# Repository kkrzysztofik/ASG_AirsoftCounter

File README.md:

Schemat mocno uproszczony, bez masy, ani zasilania. Same kable sygnałowe. Do otworzenia w progamie http://fritzing.org/home/

Budowa i części opisane w temacie:
https://forbot.pl/forum/topic/12780-airsoftowy-gadzet-koparka-airsoftcoin/

Filmik z działania: https://www.youtube.com/watch?v=qoA_SEkDOQQ

Przy pierwszym uruchomieniu trzeba odkomentować linijkę 27 z pliku System.cpp, żeby wgrać podstawowe ustawienia. Następnie trzeba uruchomić urządzenie, zakomentować linijkę ponownie i wgrać program ponownie. Dopiero wtedy zapis ustawień będzie działał poprawnie. 

Licencja mit, więc można budować, przerabiać, a nawet sprzedawać.

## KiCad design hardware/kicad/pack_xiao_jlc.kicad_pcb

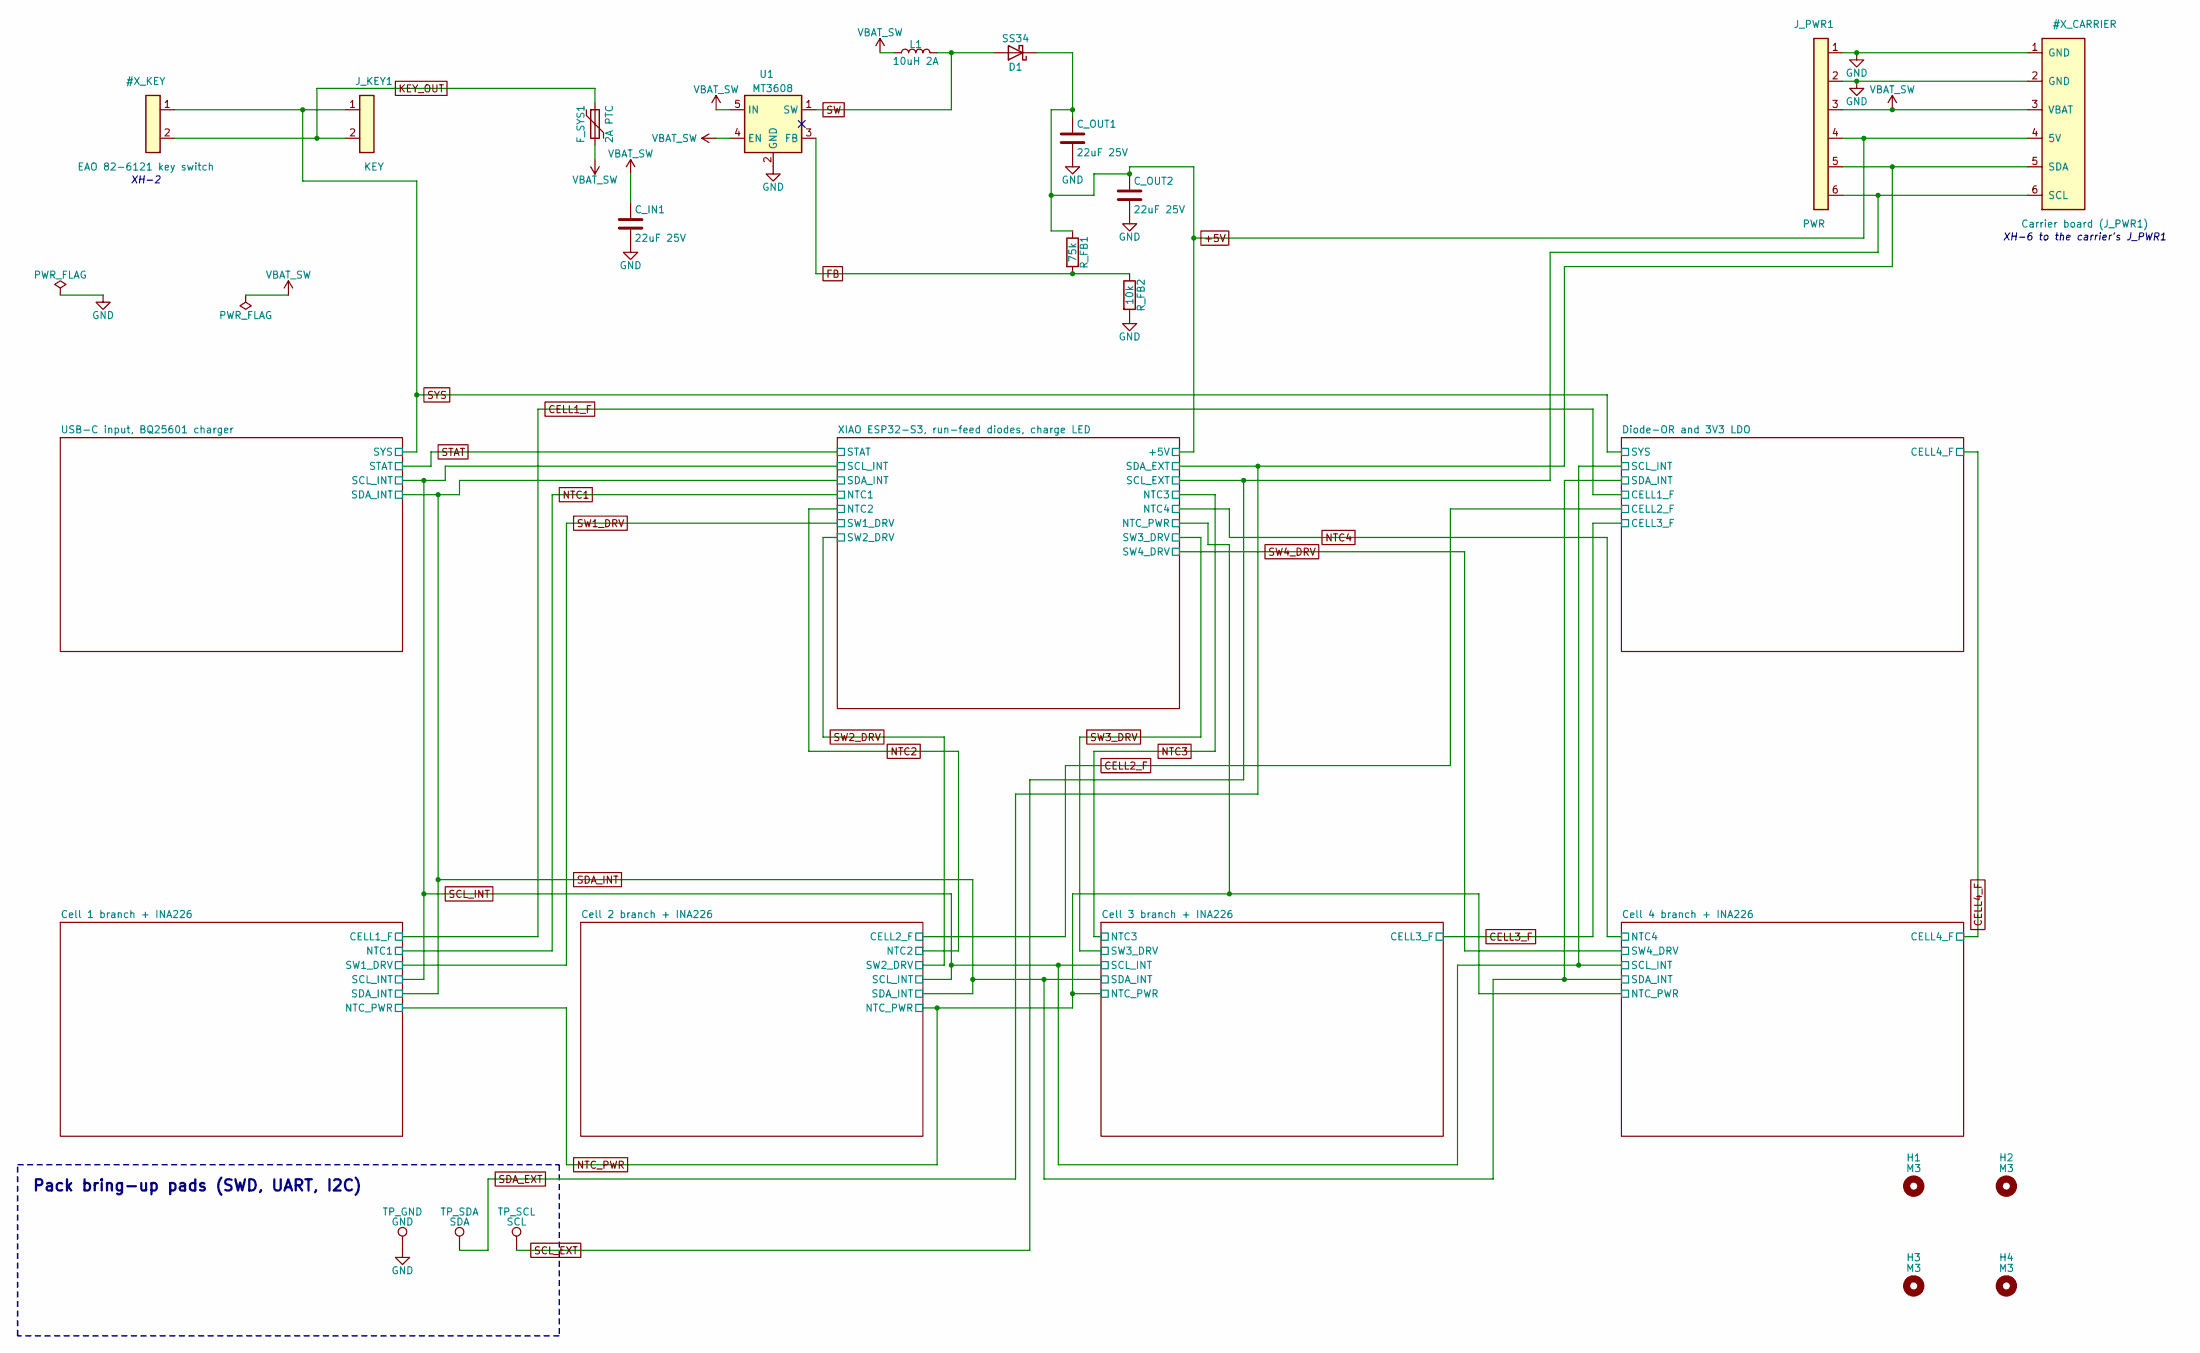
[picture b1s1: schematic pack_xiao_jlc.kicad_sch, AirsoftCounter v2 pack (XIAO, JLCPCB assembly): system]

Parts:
C_IN1: 22uF 25V; C_1206_3216Metric_Pad1.33x1.80mm_HandSolder
C_OUT1, C_OUT2: 22uF 25V; C_1206_3216Metric_Pad1.33x1.80mm_HandSolder
D1: SS34; D_SMA
F_SYS1: 2A PTC; Fuse_1206_3216Metric_Pad1.42x1.75mm_HandSolder
H1, H2, H3, H4: M3; MountingHole_3.2mm_M3
J_KEY1: KEY; JST_XH_B2B-XH-A_1x02_P2.50mm_Vertical
J_PWR1: PWR; JST_XH_B6B-XH-A_1x06_P2.50mm_Vertical
L1: 10uH 2A; L_Bourns_SRN6045TA
R_FB1: 75k; R_0805_2012Metric_Pad1.20x1.40mm_HandSolder
R_FB2: 10k; R_0805_2012Metric_Pad1.20x1.40mm_HandSolder
TP_GND: GND; TestPoint_Pad_D1.5mm
TP_SCL: SCL; TestPoint_Pad_D1.5mm
TP_SDA: SDA; TestPoint_Pad_D1.5mm
U1: MT3608; SOT-23-6

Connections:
FB: R_FB1.2, R_FB2.1, U1.3 (FB)
SW: D1.2 (A), L1.2, U1.1 (SW)

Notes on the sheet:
XH-6 to the carrier's J_PWR1
XH-2
Pack bring-up pads (SWD, UART, I2C)

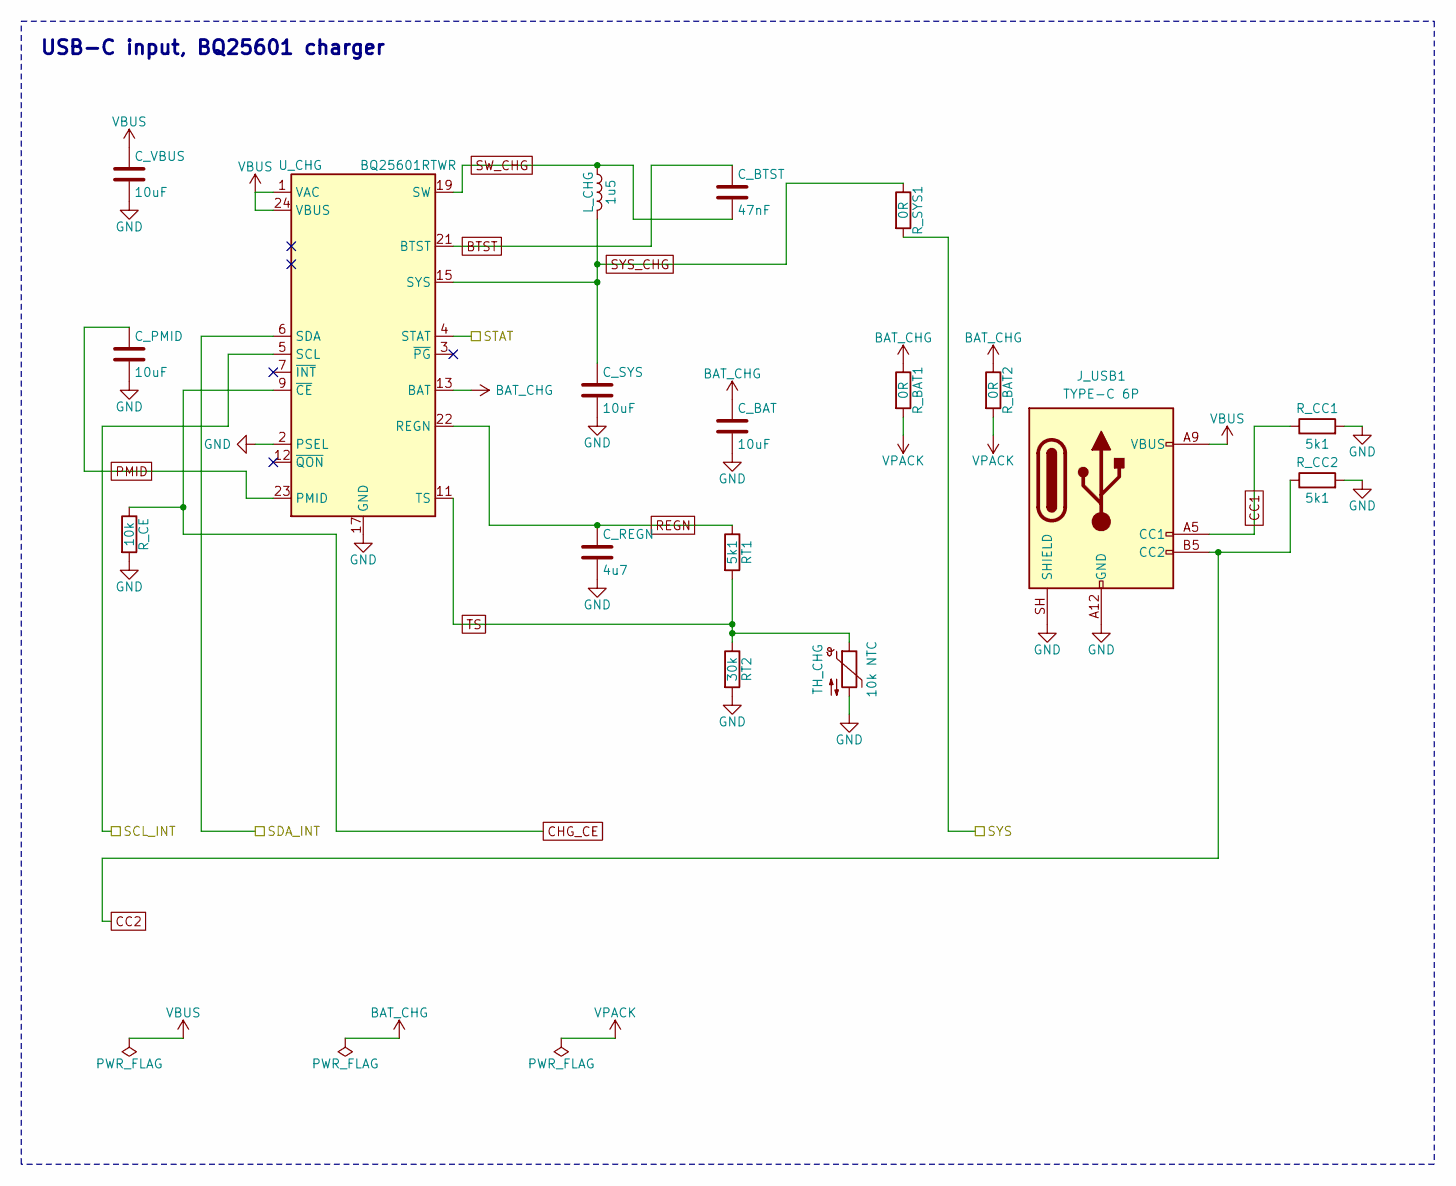
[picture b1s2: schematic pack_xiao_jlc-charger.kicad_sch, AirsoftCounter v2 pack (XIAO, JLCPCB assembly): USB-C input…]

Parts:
C_BAT: 10uF; C_0805_2012Metric_Pad1.18x1.45mm_HandSolder
C_BTST: 47nF; C_0805_2012Metric_Pad1.18x1.45mm_HandSolder
C_PMID: 10uF; C_0805_2012Metric_Pad1.18x1.45mm_HandSolder
C_REGN: 4u7; C_0805_2012Metric_Pad1.18x1.45mm_HandSolder
C_SYS: 10uF; C_0805_2012Metric_Pad1.18x1.45mm_HandSolder
C_VBUS: 10uF; C_0805_2012Metric_Pad1.18x1.45mm_HandSolder
J_USB1: TYPE-C 6P; TYPE-C-6P_C456012
L_CHG: 1u5; L_1210_3225Metric_Pad1.42x2.65mm_HandSolder
RT1: 5k1; R_0805_2012Metric_Pad1.20x1.40mm_HandSolder
RT2: 30k; R_0805_2012Metric_Pad1.20x1.40mm_HandSolder
R_BAT1, R_BAT2: 0R; R_1206_3216Metric_Pad1.30x1.75mm_HandSolder
R_CC1, R_CC2: 5k1; R_0805_2012Metric_Pad1.20x1.40mm_HandSolder
R_CE: 10k; R_0805_2012Metric_Pad1.20x1.40mm_HandSolder
R_SYS1: 0R; R_1206_3216Metric_Pad1.30x1.75mm_HandSolder
TH_CHG: 10k NTC; R_0805_2012Metric_Pad1.20x1.40mm_HandSolder
U_CHG: BQ25601RTWR; QFN-24-1EP_4x4mm_P0.5mm_EP2.6x2.6mm

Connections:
BAT_CHG: C_BAT.1, R_BAT1.1, R_BAT2.1, U_CHG.13 (BAT), U_CHG.14 (BAT)
BTST: C_BTST.1, U_CHG.21 (BTST)
CC1: J_USB1.A5 (CC1), R_CC1.1
CC2: J_USB1.B5 (CC2), R_CC2.1
CHG_CE: R_CE.1, U_CHG.9 (~CE)
PMID: C_PMID.1, U_CHG.23 (PMID)
REGN: C_REGN.1, RT1.1, U_CHG.22 (REGN)
SCL_INT: U_CHG.5 (SCL); also elsewhere on the board
SDA_INT: U_CHG.6 (SDA); also elsewhere on the board
STAT: U_CHG.4 (STAT); also elsewhere on the board
SW_CHG: C_BTST.2, L_CHG.1, U_CHG.19 (SW), U_CHG.20 (SW)
SYS_CHG: C_SYS.1, L_CHG.2, R_SYS1.1, U_CHG.15 (SYS), U_CHG.16 (SYS)
TS: RT1.2, RT2.1, TH_CHG.1, U_CHG.11 (TS)
VBUS: C_VBUS.1, J_USB1.A9 (VBUS), J_USB1.B9 (VBUS), U_CHG.1 (VAC), U_CHG.24 (VBUS); also elsewhere on the board
VPACK: R_BAT1.2, R_BAT2.2; also elsewhere on the board

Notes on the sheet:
USB-C input, BQ25601 charger

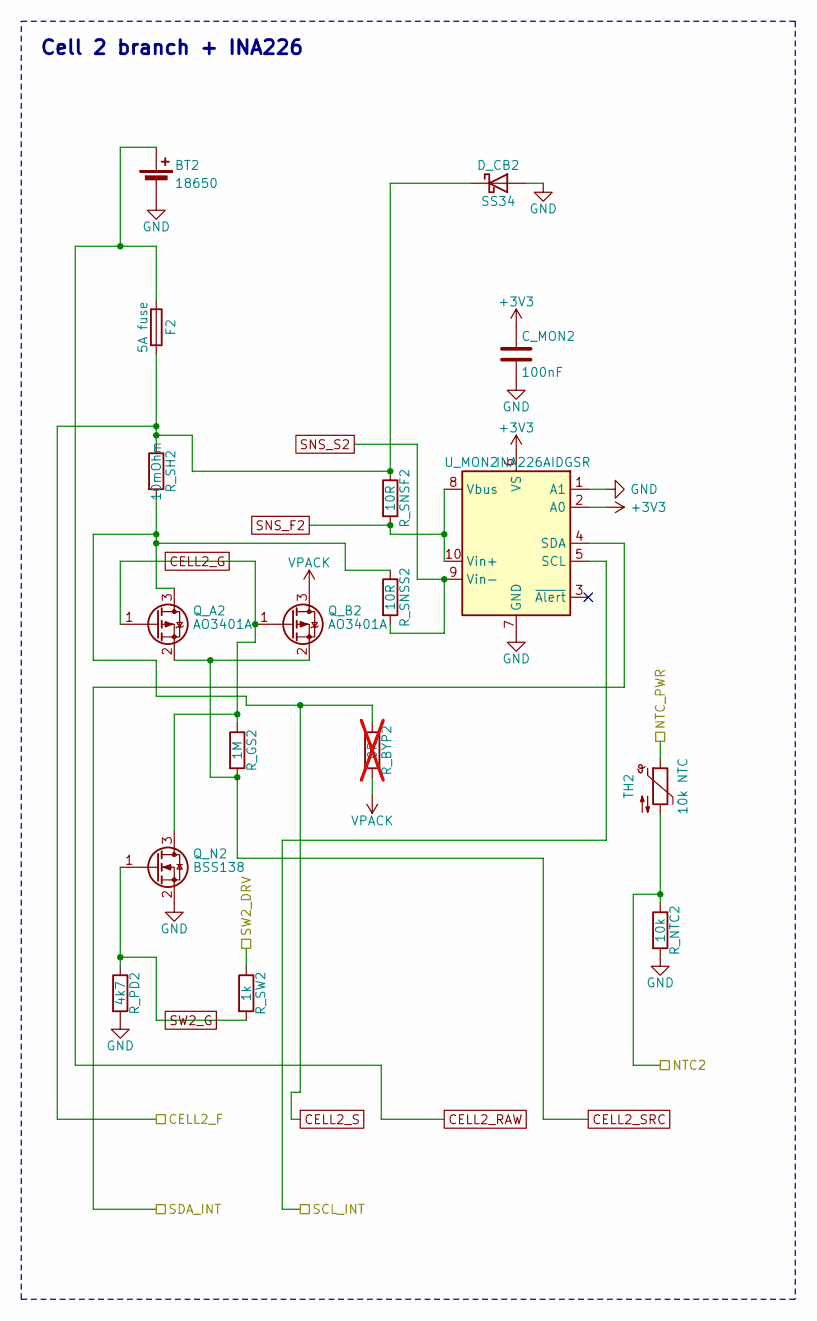
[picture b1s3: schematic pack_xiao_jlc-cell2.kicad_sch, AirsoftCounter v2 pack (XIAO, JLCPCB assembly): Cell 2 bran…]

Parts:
BT2: 18650; BatteryHolder_MYOUNG_BH-18650-A6AJ012
C_MON2: 100nF; C_0805_2012Metric_Pad1.18x1.45mm_HandSolder
D_CB2: SS34; D_SMA
F2: 5A fuse; Fuse_1206_3216Metric_Pad1.42x1.75mm_HandSolder
Q_A2: AO3401A; SOT-23
Q_B2: AO3401A; SOT-23
Q_N2: BSS138; SOT-23
R_BYP2: 0R; R_0805_2012Metric_Pad1.20x1.40mm_HandSolder; not fitted
R_GS2: 1M; R_0805_2012Metric_Pad1.20x1.40mm_HandSolder
R_NTC2: 10k; R_0805_2012Metric_Pad1.20x1.40mm_HandSolder
R_PD2: 4k7; R_0805_2012Metric_Pad1.20x1.40mm_HandSolder
R_SH2: 10mOhm; R_1206_3216Metric_Pad1.30x1.75mm_HandSolder
R_SNSF2: 10R; R_0805_2012Metric_Pad1.20x1.40mm_HandSolder
R_SNSS2: 10R; R_0805_2012Metric_Pad1.20x1.40mm_HandSolder
R_SW2: 1k; R_0805_2012Metric_Pad1.20x1.40mm_HandSolder
TH2: 10k NTC; NTC_Bead_P2.54mm
U_MON2: INA226AIDGSR; MSOP-10_3x3mm_P0.5mm

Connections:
+3V3: C_MON2.1, U_MON2.2 (A0), U_MON2.6 (VS); also elsewhere on the board
CELL2_F: D_CB2.1 (K), F2.2, R_SH2.1, R_SNSF2.1; also elsewhere on the board
CELL2_G: Q_A2.1 (G), Q_B2.1 (G), Q_N2.3 (D), R_GS2.1
CELL2_RAW: BT2.1 (+), F2.1
CELL2_S: Q_A2.3 (D), R_BYP2.1, R_SH2.2, R_SNSS2.1
CELL2_SRC: Q_A2.2 (S), Q_B2.2 (S), R_GS2.2
NTC2: R_NTC2.1, TH2.2; also elsewhere on the board
NTC_PWR: TH2.1; also elsewhere on the board
SCL_INT: U_MON2.5 (SCL); also elsewhere on the board
SDA_INT: U_MON2.4 (SDA); also elsewhere on the board
SNS_F2: R_SNSF2.2, U_MON2.8 (Vbus), U_MON2.10 (Vin+)
SNS_S2: R_SNSS2.2, U_MON2.9 (Vin-)
SW2_DRV: R_SW2.1; also elsewhere on the board
SW2_G: Q_N2.1 (G), R_PD2.1, R_SW2.2
VPACK: Q_B2.3 (D), R_BYP2.2; also elsewhere on the board

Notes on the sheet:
Cell 2 branch + INA226

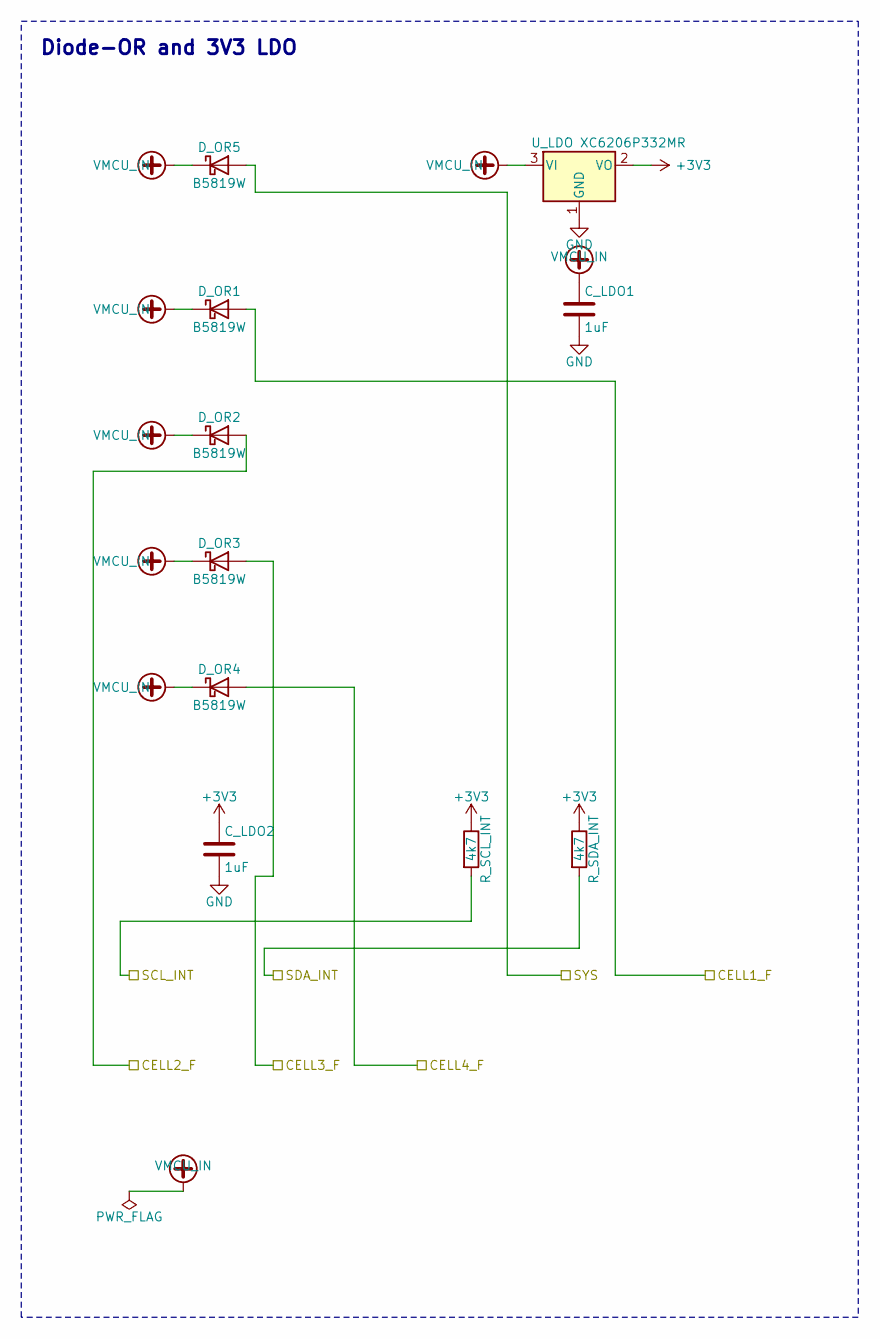
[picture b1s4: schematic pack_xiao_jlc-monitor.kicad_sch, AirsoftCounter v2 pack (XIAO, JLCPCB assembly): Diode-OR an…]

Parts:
C_LDO1, C_LDO2: 1uF; C_0805_2012Metric_Pad1.18x1.45mm_HandSolder
D_OR1, D_OR2, D_OR3, D_OR4, D_OR5: B5819W; D_SOD-123
R_SCL_INT: 4k7; R_0805_2012Metric_Pad1.20x1.40mm_HandSolder
R_SDA_INT: 4k7; R_0805_2012Metric_Pad1.20x1.40mm_HandSolder
U_LDO: XC6206P332MR; SOT-23-3

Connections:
+3V3: C_LDO2.1, R_SCL_INT.1, R_SDA_INT.1, U_LDO.2 (VO); also elsewhere on the board
CELL1_F: D_OR1.2 (A); also elsewhere on the board
CELL2_F: D_OR2.2 (A); also elsewhere on the board
CELL3_F: D_OR3.2 (A); also elsewhere on the board
CELL4_F: D_OR4.2 (A); also elsewhere on the board
SCL_INT: R_SCL_INT.2; also elsewhere on the board
SDA_INT: R_SDA_INT.2; also elsewhere on the board
VMCU_IN: C_LDO1.1, D_OR1.1 (K), D_OR2.1 (K), D_OR3.1 (K), D_OR4.1 (K), D_OR5.1 (K), U_LDO.3 (VI)

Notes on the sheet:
Diode-OR and 3V3 LDO

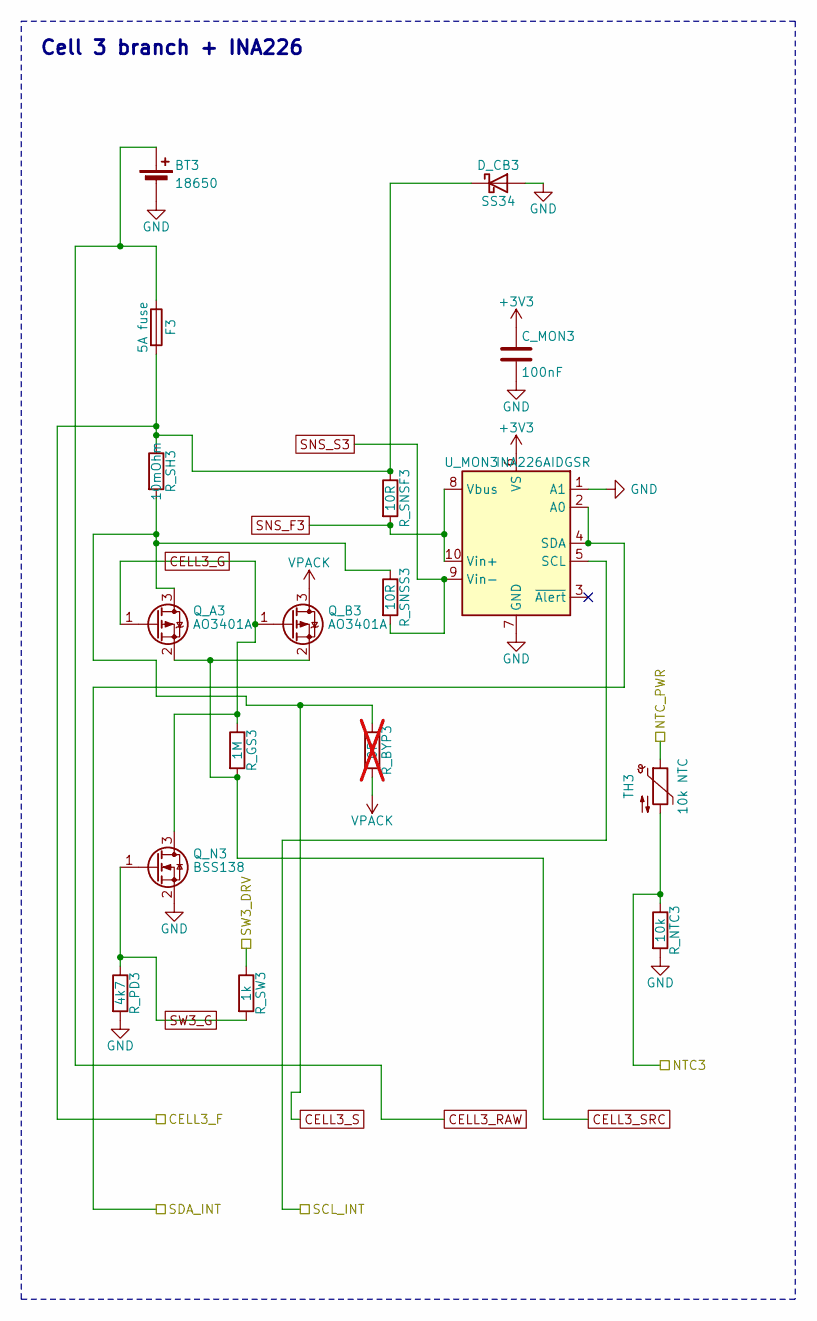
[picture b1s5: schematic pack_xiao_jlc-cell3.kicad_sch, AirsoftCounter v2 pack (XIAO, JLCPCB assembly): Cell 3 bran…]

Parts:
BT3: 18650; BatteryHolder_MYOUNG_BH-18650-A6AJ012
C_MON3: 100nF; C_0805_2012Metric_Pad1.18x1.45mm_HandSolder
D_CB3: SS34; D_SMA
F3: 5A fuse; Fuse_1206_3216Metric_Pad1.42x1.75mm_HandSolder
Q_A3: AO3401A; SOT-23
Q_B3: AO3401A; SOT-23
Q_N3: BSS138; SOT-23
R_BYP3: 0R; R_0805_2012Metric_Pad1.20x1.40mm_HandSolder; not fitted
R_GS3: 1M; R_0805_2012Metric_Pad1.20x1.40mm_HandSolder
R_NTC3: 10k; R_0805_2012Metric_Pad1.20x1.40mm_HandSolder
R_PD3: 4k7; R_0805_2012Metric_Pad1.20x1.40mm_HandSolder
R_SH3: 10mOhm; R_1206_3216Metric_Pad1.30x1.75mm_HandSolder
R_SNSF3: 10R; R_0805_2012Metric_Pad1.20x1.40mm_HandSolder
R_SNSS3: 10R; R_0805_2012Metric_Pad1.20x1.40mm_HandSolder
R_SW3: 1k; R_0805_2012Metric_Pad1.20x1.40mm_HandSolder
TH3: 10k NTC; NTC_Bead_P2.54mm
U_MON3: INA226AIDGSR; MSOP-10_3x3mm_P0.5mm

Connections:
+3V3: C_MON3.1, U_MON3.6 (VS); also elsewhere on the board
CELL3_F: D_CB3.1 (K), F3.2, R_SH3.1, R_SNSF3.1; also elsewhere on the board
CELL3_G: Q_A3.1 (G), Q_B3.1 (G), Q_N3.3 (D), R_GS3.1
CELL3_RAW: BT3.1 (+), F3.1
CELL3_S: Q_A3.3 (D), R_BYP3.1, R_SH3.2, R_SNSS3.1
CELL3_SRC: Q_A3.2 (S), Q_B3.2 (S), R_GS3.2
NTC3: R_NTC3.1, TH3.2; also elsewhere on the board
NTC_PWR: TH3.1; also elsewhere on the board
SCL_INT: U_MON3.5 (SCL); also elsewhere on the board
SDA_INT: U_MON3.2 (A0), U_MON3.4 (SDA); also elsewhere on the board
SNS_F3: R_SNSF3.2, U_MON3.8 (Vbus), U_MON3.10 (Vin+)
SNS_S3: R_SNSS3.2, U_MON3.9 (Vin-)
SW3_DRV: R_SW3.1; also elsewhere on the board
SW3_G: Q_N3.1 (G), R_PD3.1, R_SW3.2
VPACK: Q_B3.3 (D), R_BYP3.2; also elsewhere on the board

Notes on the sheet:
Cell 3 branch + INA226

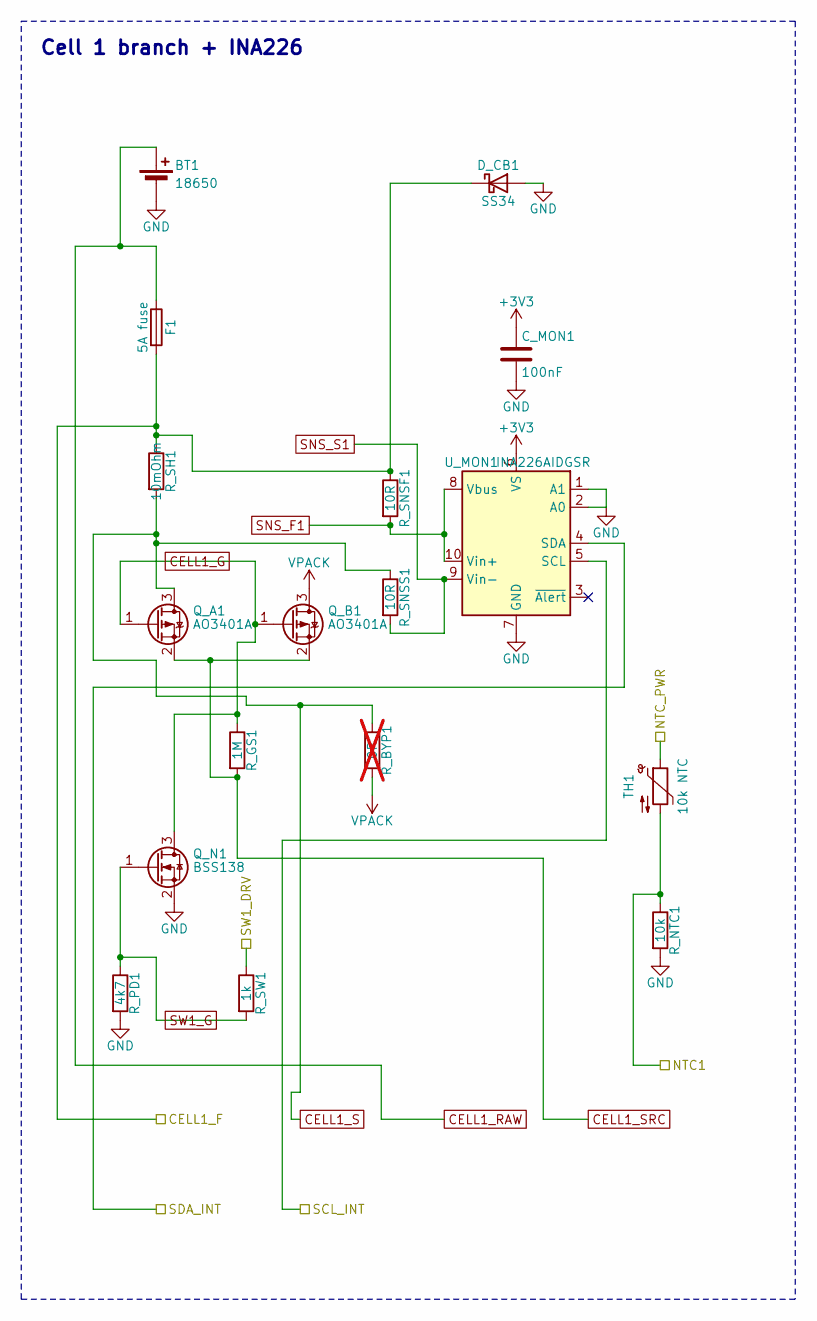
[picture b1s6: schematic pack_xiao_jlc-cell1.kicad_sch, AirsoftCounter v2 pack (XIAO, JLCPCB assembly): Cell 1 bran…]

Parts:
BT1: 18650; BatteryHolder_MYOUNG_BH-18650-A6AJ012
C_MON1: 100nF; C_0805_2012Metric_Pad1.18x1.45mm_HandSolder
D_CB1: SS34; D_SMA
F1: 5A fuse; Fuse_1206_3216Metric_Pad1.42x1.75mm_HandSolder
Q_A1: AO3401A; SOT-23
Q_B1: AO3401A; SOT-23
Q_N1: BSS138; SOT-23
R_BYP1: 0R; R_0805_2012Metric_Pad1.20x1.40mm_HandSolder; not fitted
R_GS1: 1M; R_0805_2012Metric_Pad1.20x1.40mm_HandSolder
R_NTC1: 10k; R_0805_2012Metric_Pad1.20x1.40mm_HandSolder
R_PD1: 4k7; R_0805_2012Metric_Pad1.20x1.40mm_HandSolder
R_SH1: 10mOhm; R_1206_3216Metric_Pad1.30x1.75mm_HandSolder
R_SNSF1: 10R; R_0805_2012Metric_Pad1.20x1.40mm_HandSolder
R_SNSS1: 10R; R_0805_2012Metric_Pad1.20x1.40mm_HandSolder
R_SW1: 1k; R_0805_2012Metric_Pad1.20x1.40mm_HandSolder
TH1: 10k NTC; NTC_Bead_P2.54mm
U_MON1: INA226AIDGSR; MSOP-10_3x3mm_P0.5mm

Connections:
+3V3: C_MON1.1, U_MON1.6 (VS); also elsewhere on the board
CELL1_F: D_CB1.1 (K), F1.2, R_SH1.1, R_SNSF1.1; also elsewhere on the board
CELL1_G: Q_A1.1 (G), Q_B1.1 (G), Q_N1.3 (D), R_GS1.1
CELL1_RAW: BT1.1 (+), F1.1
CELL1_S: Q_A1.3 (D), R_BYP1.1, R_SH1.2, R_SNSS1.1
CELL1_SRC: Q_A1.2 (S), Q_B1.2 (S), R_GS1.2
NTC1: R_NTC1.1, TH1.2; also elsewhere on the board
NTC_PWR: TH1.1; also elsewhere on the board
SCL_INT: U_MON1.5 (SCL); also elsewhere on the board
SDA_INT: U_MON1.4 (SDA); also elsewhere on the board
SNS_F1: R_SNSF1.2, U_MON1.8 (Vbus), U_MON1.10 (Vin+)
SNS_S1: R_SNSS1.2, U_MON1.9 (Vin-)
SW1_DRV: R_SW1.1; also elsewhere on the board
SW1_G: Q_N1.1 (G), R_PD1.1, R_SW1.2
VPACK: Q_B1.3 (D), R_BYP1.2; also elsewhere on the board

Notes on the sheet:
Cell 1 branch + INA226

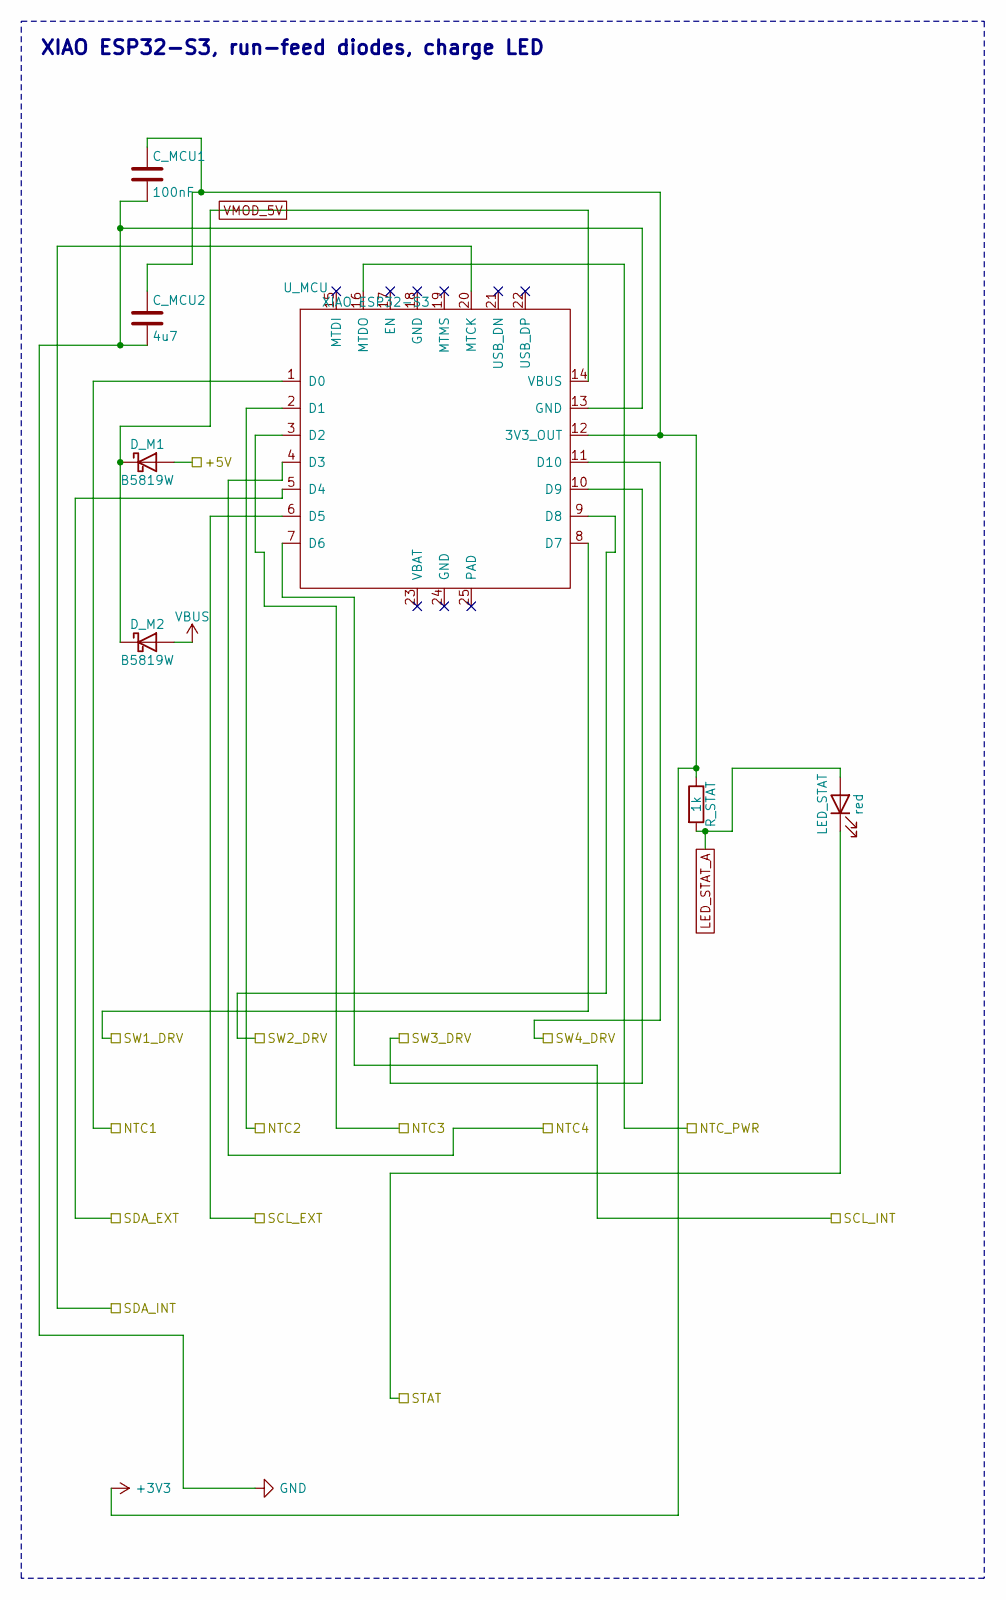
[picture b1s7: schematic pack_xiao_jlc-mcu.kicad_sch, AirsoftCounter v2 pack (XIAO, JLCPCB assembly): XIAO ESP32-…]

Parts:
C_MCU1: 100nF; C_0805_2012Metric_Pad1.18x1.45mm_HandSolder
C_MCU2: 4u7; C_0805_2012Metric_Pad1.18x1.45mm_HandSolder
D_M1, D_M2: B5819W; D_SOD-123
LED_STAT: red; LED_0805_2012Metric_Pad1.15x1.40mm_HandSolder
R_STAT: 1k; R_0805_2012Metric_Pad1.20x1.40mm_HandSolder
U_MCU: XIAO ESP32-S3; XIAO_ESP32S3_SMD_THB

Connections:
+3V3: C_MCU1.1, C_MCU2.1, R_STAT.1, U_MCU.12 (3V3_OUT); also elsewhere on the board
LED_STAT_A: LED_STAT.2 (A), R_STAT.2
NTC1: U_MCU.1 (D0); also elsewhere on the board
NTC2: U_MCU.2 (D1); also elsewhere on the board
NTC3: U_MCU.3 (D2); also elsewhere on the board
NTC4: U_MCU.4 (D3); also elsewhere on the board
NTC_PWR: U_MCU.16 (MTDO); also elsewhere on the board
SCL_INT: U_MCU.7 (D6); also elsewhere on the board
SDA_INT: U_MCU.20 (MTCK); also elsewhere on the board
STAT: LED_STAT.1 (K); also elsewhere on the board
SW1_DRV: U_MCU.8 (D7); also elsewhere on the board
SW2_DRV: U_MCU.9 (D8); also elsewhere on the board
SW3_DRV: U_MCU.10 (D9); also elsewhere on the board
SW4_DRV: U_MCU.11 (D10); also elsewhere on the board
VBUS: D_M2.2 (A); also elsewhere on the board
VMOD_5V: D_M1.1 (K), D_M2.1 (K), U_MCU.14 (VBUS)

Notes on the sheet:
XIAO ESP32-S3, run-feed diodes, charge LED

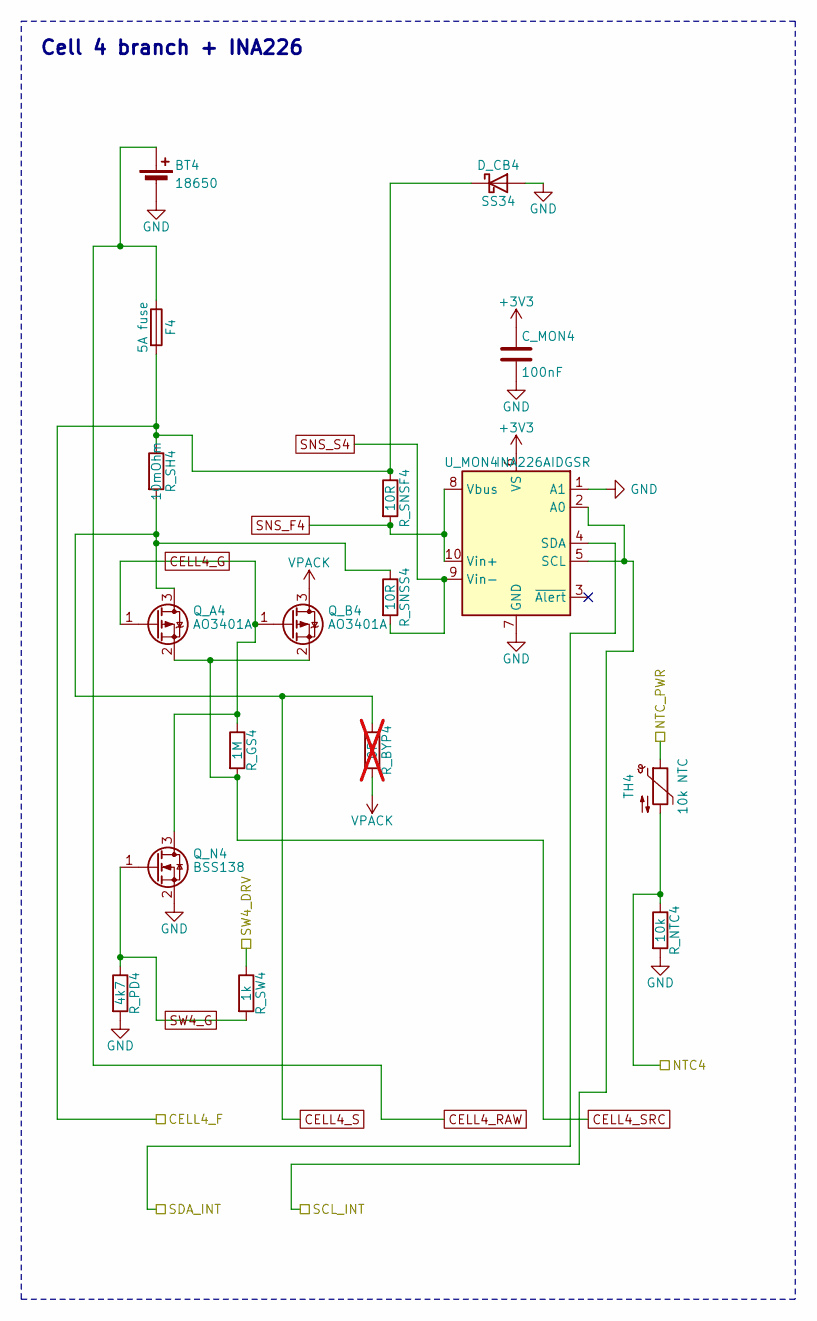
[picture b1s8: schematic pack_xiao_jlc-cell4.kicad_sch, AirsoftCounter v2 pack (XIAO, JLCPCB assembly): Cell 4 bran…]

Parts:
BT4: 18650; BatteryHolder_MYOUNG_BH-18650-A6AJ012
C_MON4: 100nF; C_0805_2012Metric_Pad1.18x1.45mm_HandSolder
D_CB4: SS34; D_SMA
F4: 5A fuse; Fuse_1206_3216Metric_Pad1.42x1.75mm_HandSolder
Q_A4: AO3401A; SOT-23
Q_B4: AO3401A; SOT-23
Q_N4: BSS138; SOT-23
R_BYP4: 0R; R_0805_2012Metric_Pad1.20x1.40mm_HandSolder; not fitted
R_GS4: 1M; R_0805_2012Metric_Pad1.20x1.40mm_HandSolder
R_NTC4: 10k; R_0805_2012Metric_Pad1.20x1.40mm_HandSolder
R_PD4: 4k7; R_0805_2012Metric_Pad1.20x1.40mm_HandSolder
R_SH4: 10mOhm; R_1206_3216Metric_Pad1.30x1.75mm_HandSolder
R_SNSF4: 10R; R_0805_2012Metric_Pad1.20x1.40mm_HandSolder
R_SNSS4: 10R; R_0805_2012Metric_Pad1.20x1.40mm_HandSolder
R_SW4: 1k; R_0805_2012Metric_Pad1.20x1.40mm_HandSolder
TH4: 10k NTC; NTC_Bead_P2.54mm
U_MON4: INA226AIDGSR; MSOP-10_3x3mm_P0.5mm

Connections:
+3V3: C_MON4.1, U_MON4.6 (VS); also elsewhere on the board
CELL4_F: D_CB4.1 (K), F4.2, R_SH4.1, R_SNSF4.1; also elsewhere on the board
CELL4_G: Q_A4.1 (G), Q_B4.1 (G), Q_N4.3 (D), R_GS4.1
CELL4_RAW: BT4.1 (+), F4.1
CELL4_S: Q_A4.3 (D), R_BYP4.1, R_SH4.2, R_SNSS4.1
CELL4_SRC: Q_A4.2 (S), Q_B4.2 (S), R_GS4.2
NTC4: R_NTC4.1, TH4.2; also elsewhere on the board
NTC_PWR: TH4.1; also elsewhere on the board
SCL_INT: U_MON4.2 (A0), U_MON4.5 (SCL); also elsewhere on the board
SDA_INT: U_MON4.4 (SDA); also elsewhere on the board
SNS_F4: R_SNSF4.2, U_MON4.8 (Vbus), U_MON4.10 (Vin+)
SNS_S4: R_SNSS4.2, U_MON4.9 (Vin-)
SW4_DRV: R_SW4.1; also elsewhere on the board
SW4_G: Q_N4.1 (G), R_PD4.1, R_SW4.2
VPACK: Q_B4.3 (D), R_BYP4.2; also elsewhere on the board

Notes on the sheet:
Cell 4 branch + INA226

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
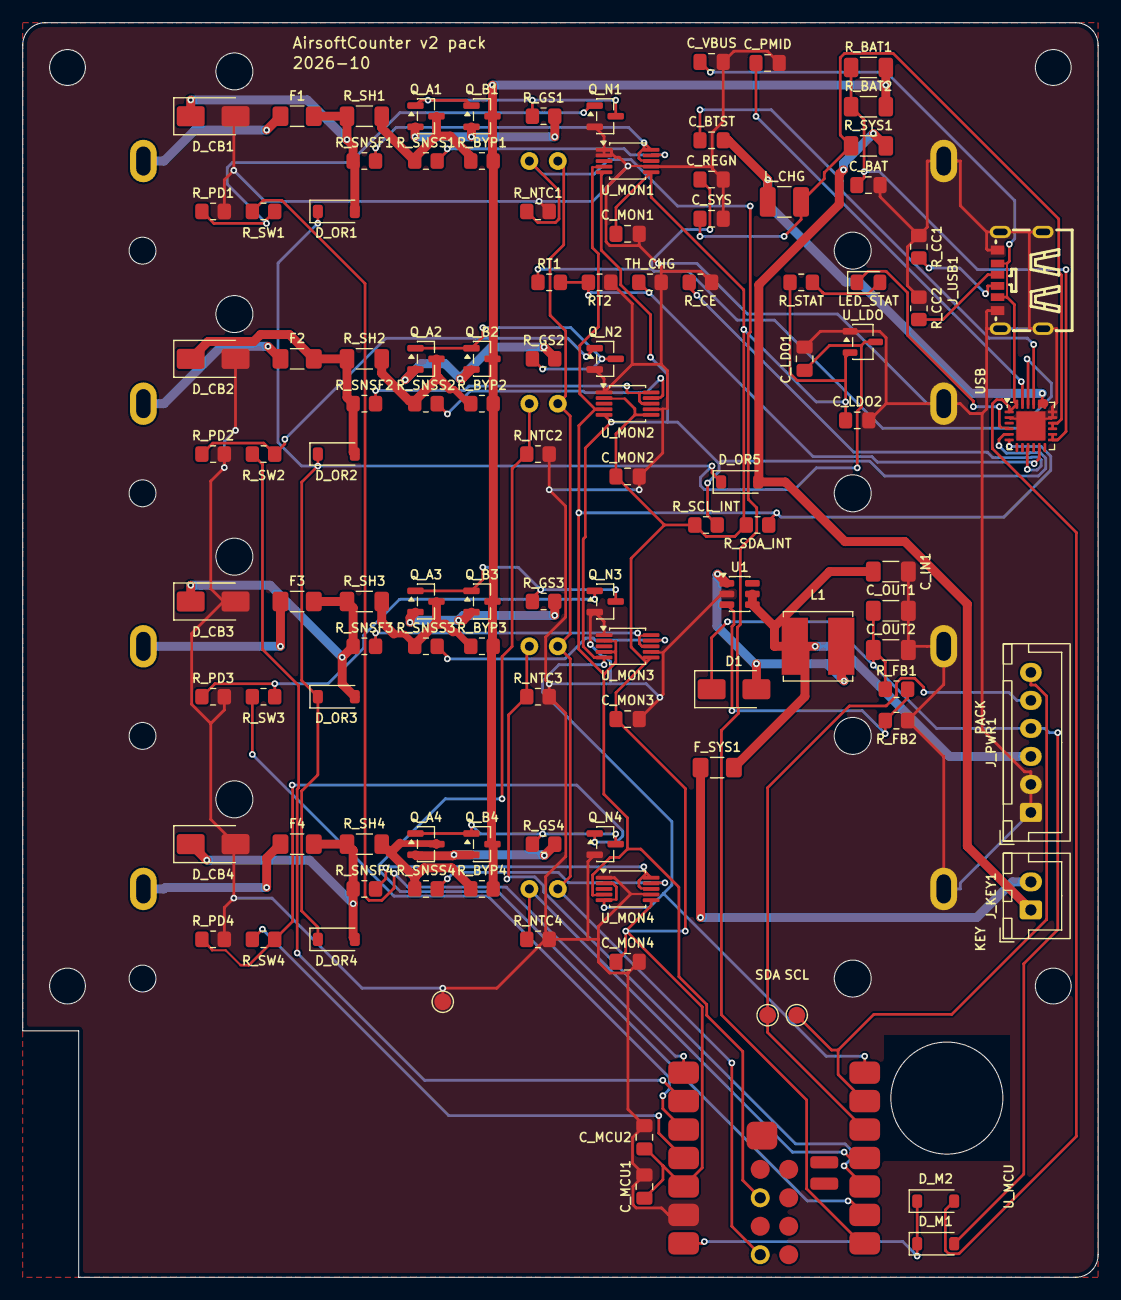
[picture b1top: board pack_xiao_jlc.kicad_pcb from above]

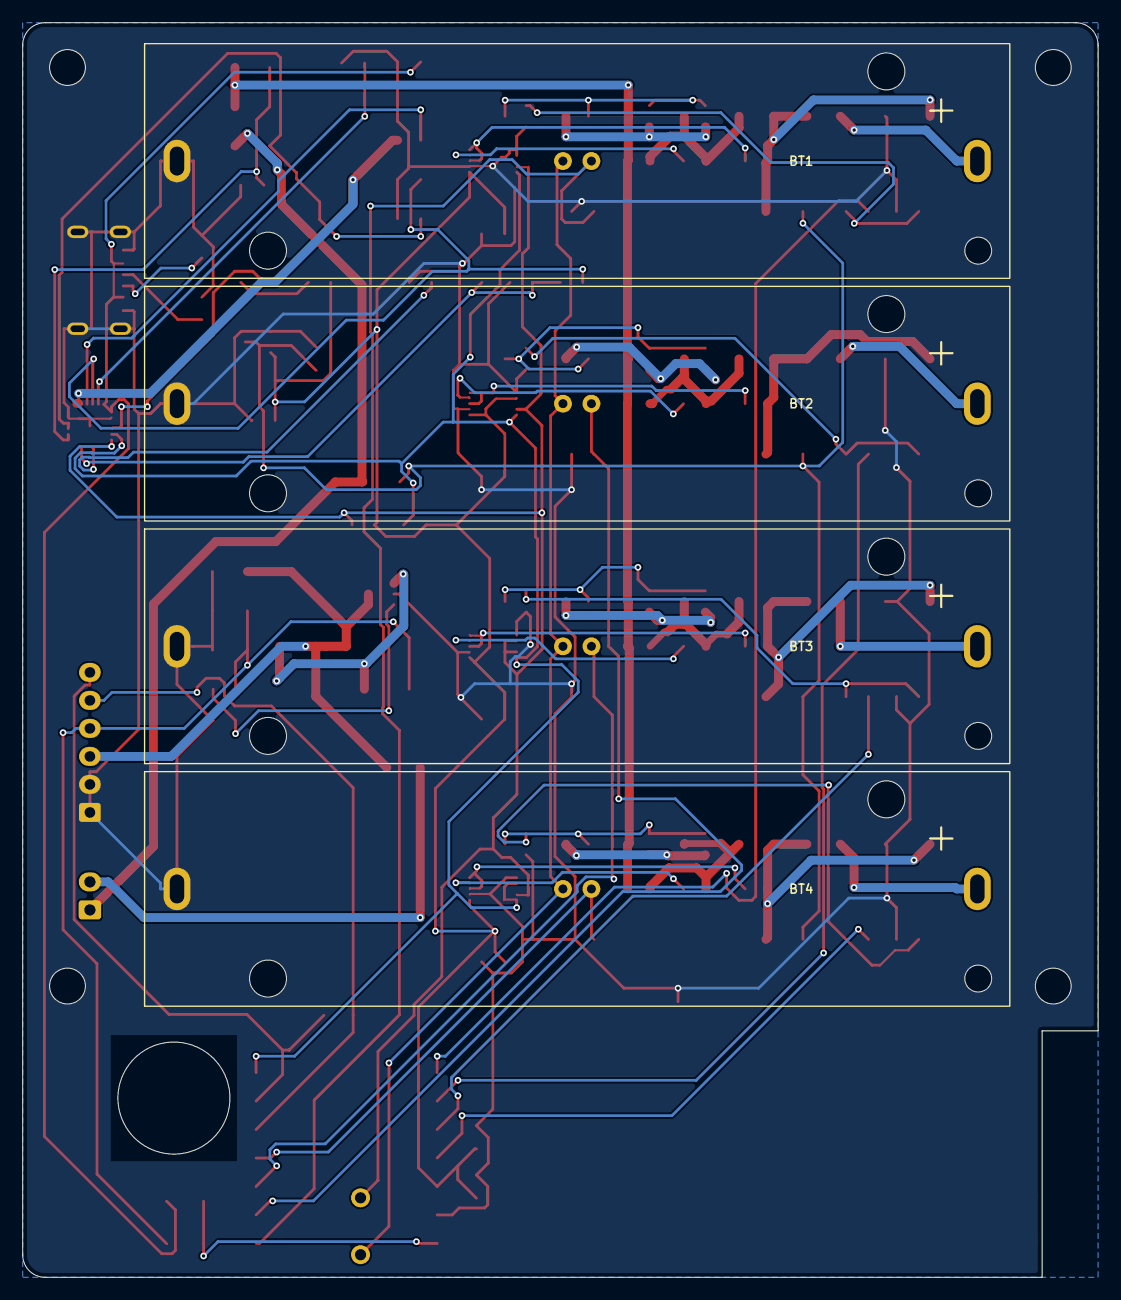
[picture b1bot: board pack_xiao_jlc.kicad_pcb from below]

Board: 2 copper layers, 96.0 x 112.0 mm, 121 parts (8 on the bottom side), 69 nets.
